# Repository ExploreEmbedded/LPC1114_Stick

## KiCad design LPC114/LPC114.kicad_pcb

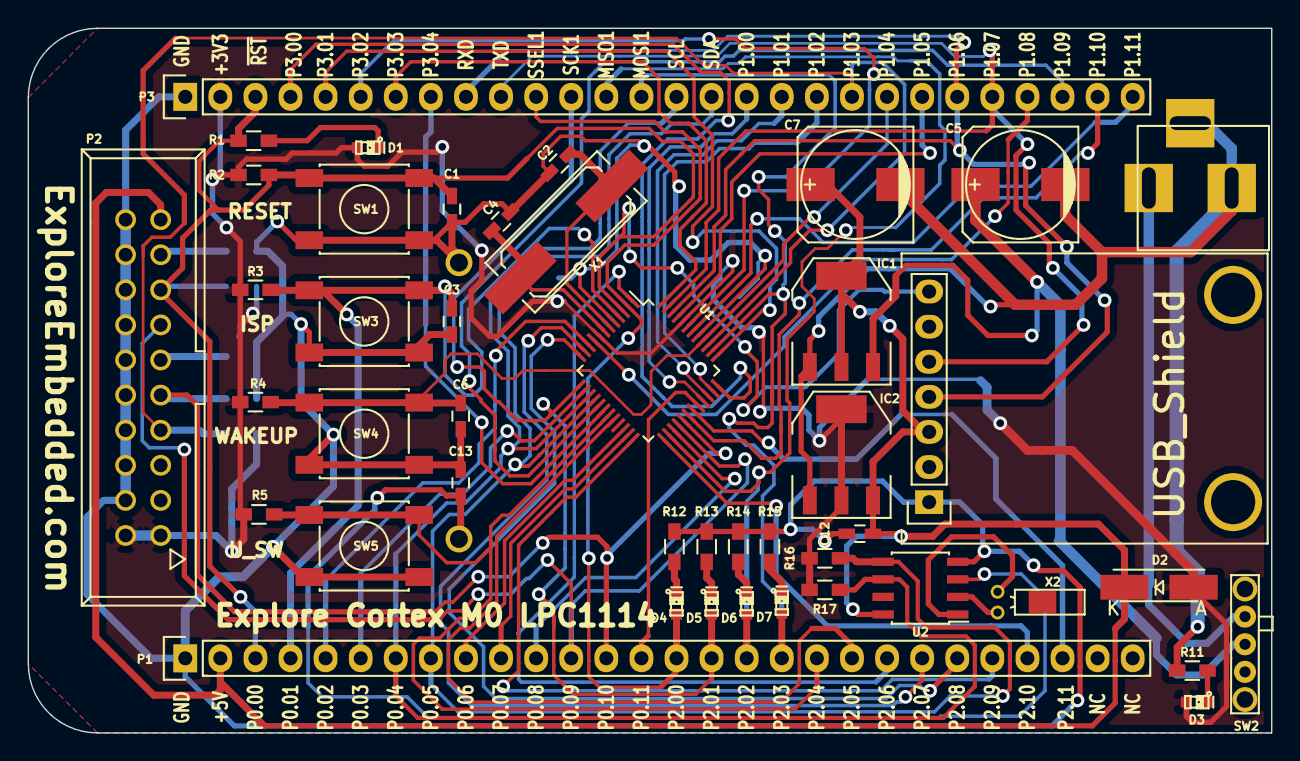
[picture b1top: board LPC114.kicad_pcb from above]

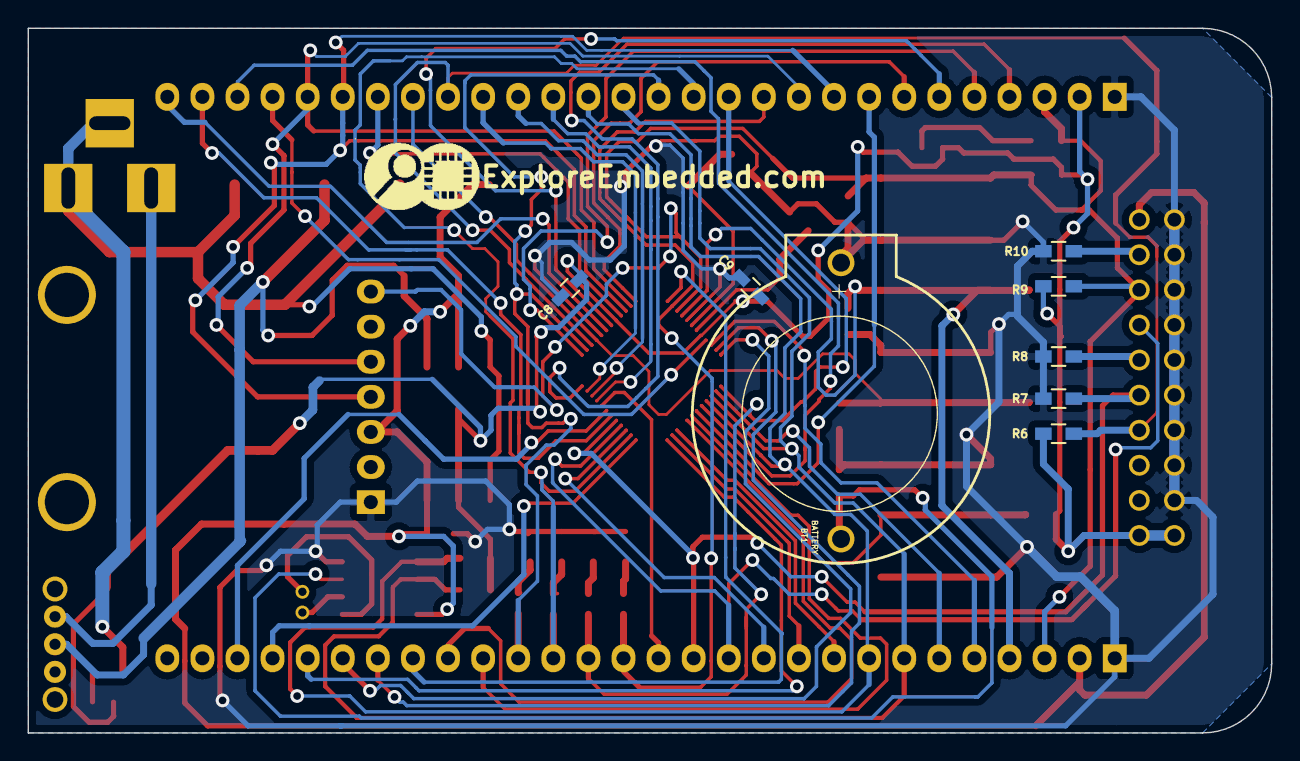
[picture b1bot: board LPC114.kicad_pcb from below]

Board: 2 copper layers, 90.0 x 51.0 mm, 53 parts (9 on the bottom side), 60 nets.

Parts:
BT1: BATTERY; BATT_rtc_XL
C1, C3, C6, C8, C9, C12, C13: 0.1uF; C_0603_HandSoldering
C2, C4: 22PF; C_0603_HandSoldering
C5, C7: 100uF/25V; c_elec_8x10.5
CON1: BARREL_JACK
D1, D3, D4, D5, D6, D7: LED; LED-0603_NEW
D2: IN4148; ZenerDiode_SMD
IC1, IC2: LM1117; SOT-223
LOGO: LOGO (2)
P1, P3: CONN_01X28; Pin_Header_Straight_1x28
P2: JTAG; VASCH10x2
P4: CONN_01X07; USB_Shield
R1, R11, R12, R13, R14, R15: 470E; R_0603_HandSoldering
R2, R5, R6, R7, R8, R9, R10, R16, R17: 10K; R_0603_HandSoldering
R3, R4: 1K; R_0603_HandSoldering
SW1, SW3, SW4, SW5: SW_PUSH; SW_PUSH_SMALL_smd_NEW
SW2: SPST; Micro_slide_switch-spst_2mm_new
U1: LPC1114FBD48/302; LQFP-48_7x7mm_Pitch0.5mm
U2: DS1307N+; SOIC-8_3.9x4.9mm_Pitch1.27mm
X1: 12MHZ; Q_49U3HMS
X2: 3.768KHz; Crystal_Round_Horizontal_2mm_NEW

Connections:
+3.3VP: C8.1, C9.1, D1.1, D2.1, D3.1, IC2.2, IC2.4, P2.1, P2.2, P3.2, R2.1, R3.1, R4.1, R5.1, R6.2, R9.2, R16.2, R17.2, U1.8, U1.44
+5V: C7.1, C12.2, D2.2, IC1.2, IC1.4, IC2.3, P1.2, P2.19, P4.3, U2.8
GND: BT1.1, C1.2, C2.1, C3.2, C4.1, C6.2, C8.2, C9.2, C12.1, C13.2, P1.1, P2.4, P2.6, P2.8, P2.10, P2.12, P2.14, P2.16, P2.18, P2.20, P3.1, P4.1, R7.2, R8.2, R10.2, R12.1, R13.1, R14.1, R15.1, SW1.2, SW3.2, SW4.2, SW5.2, U1.5, U1.41, U2.4
ISP: C3.1, P1.4, R3.2, SW3.1, U1.4
unnamed: BT1.2, C13.1, U2.3
unnamed: C2.2, U1.6, X1.1
unnamed: C4.2, U1.7, X1.2
unnamed: C5.1, IC1.3, SW2.2
unnamed: C5.2, C7.2, CON1.2, CON1.3, IC1.1, IC2.1, R11.2
unnamed: CON1.1, SW2.1
unnamed: D1.2, R1.1
unnamed: D3.2, R11.1
unnamed: D4.2, R12.2
unnamed: D5.2, R13.2
unnamed: D6.2, R14.2
unnamed: D7.2, R15.2
unnamed: P1.5, U1.10
unnamed: P1.6, U1.14
unnamed: P1.9, U1.22
unnamed: P1.10, U1.23
unnamed: P1.11, U1.27
unnamed: P1.14, U1.32
unnamed: P1.20, U1.20
unnamed: P2.11, R8.1
unnamed: P2.17, R10.1
unnamed: P3.17, U1.33
unnamed: P3.18, U1.34
unnamed: P3.19, U1.35
unnamed: P3.22, U1.45
unnamed: P3.25, U1.9
unnamed: P3.26, U1.17
unnamed: P3.27, U1.30
unnamed: P3.28, U1.42
unnamed: U2.1, X2.1
unnamed: U2.2, X2.2
P2_0: D4.1, P1.15, P3.11, U1.2
P2_1: D5.1, P1.16, P3.12, U1.13
P2_2: D6.1, P1.17, P3.13, U1.26
P2_3: D7.1, P1.18, P3.14, U1.38
P2_6: P1.21, U1.1
P2_7: P1.22, U1.11
P2_8: P1.23, U1.12
P2_9: P1.24, U1.24
P2_10: P1.25, U1.25
P2_11: P1.26, U1.31
P3_0: P3.4, U1.36
P3_1: P3.5, U1.37
P3_2: P3.6, U1.43
P3_3: P3.7, U1.48
P3_4: P3.8, U1.18
RESET: C1.1, P1.3, P2.15, P3.3, P4.7, R1.2, R2.2, R9.1, SW1.1, U1.3
RXD: P3.9, P3.23, P4.4, U1.46
SCL: P1.7, P3.15, R17.1, U1.15, U2.6
SDA: P1.8, P3.16, R16.1, U1.16, U2.5
SWCLK: P1.13, P2.9, R7.1, U1.29
SWDIO: P2.7, P3.20, R6.1, U1.39
SWO: P1.12, P2.13, U1.28
TXD: P3.10, P3.24, P4.5, U1.47
U_SW: P1.19, R5.2, SW5.1, U1.19
WAKEUP: C6.1, P3.21, R4.2, SW4.1, U1.40

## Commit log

2015-07-29 added reference and design files
2015-07-30 added 2nd step files
2015-08-03 added final files
2015-08-11 gerber file added
2015-08-13 Design errors
